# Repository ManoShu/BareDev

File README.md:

# BareDev - A small, yet resourceful keyboard

An open-source, QMK-compatible, ABNT2-based 70% keyboard, focusing in a smaller footprint while retaining all the functions found on a TKL (Del and arrow keys doubling as the navigational cluster)

---

Layout:

Links: [KLE](http://www.keyboard-layout-editor.com/#/gists/89e76130aa221e028ccd5b3f6dec0909), [JSON](https://gist.github.com/ManoShu/89e76130aa221e028ccd5b3f6dec0909), [QMK](https://github.com/qmk/qmk_firmware/tree/master/keyboards/handwired/baredev/rev1)

---

## PCB & Case

Note: this photo is of an early prototype of the case. The uploaded files has been updated to require less total area and WILL look slighty different than shown (the overall dimensions remain the same).

The case and gerber files are under `production`. The had been used and confirmed to work, however use them at your own risk.

## QMK

The rev1 has been integrated in the [main QMK repository](https://github.com/qmk/qmk_firmware/tree/master/keyboards/handwired/baredev/rev1), being able to use the [online configurator](https://config.qmk.fm/#/handwired/baredev/rev1/LAYOUT_abnt2) to generate the firmware while also having the files on the `qmk` directory here in case of you don't want to update your fork (HOWEVER the files have been confirmed working on QMK 0.2.2 [check yours with `qmk --version`], previous versions might not have support for some of the tags in the` info.json` file)

## VIA / VIAL

A `via` keymap is available allowing to use VIA to change keybindings without the need to setup QMK. 
It is not integrated with the official repository yet, but the .json file required to change bindings is available on the `via` directory.

A VIAL-compatible keymap is also available. It is on the official repository, but in case you don't want to update, just drop the keyboard folder to your `vial-qmk` directory and it should also work right off the bat.

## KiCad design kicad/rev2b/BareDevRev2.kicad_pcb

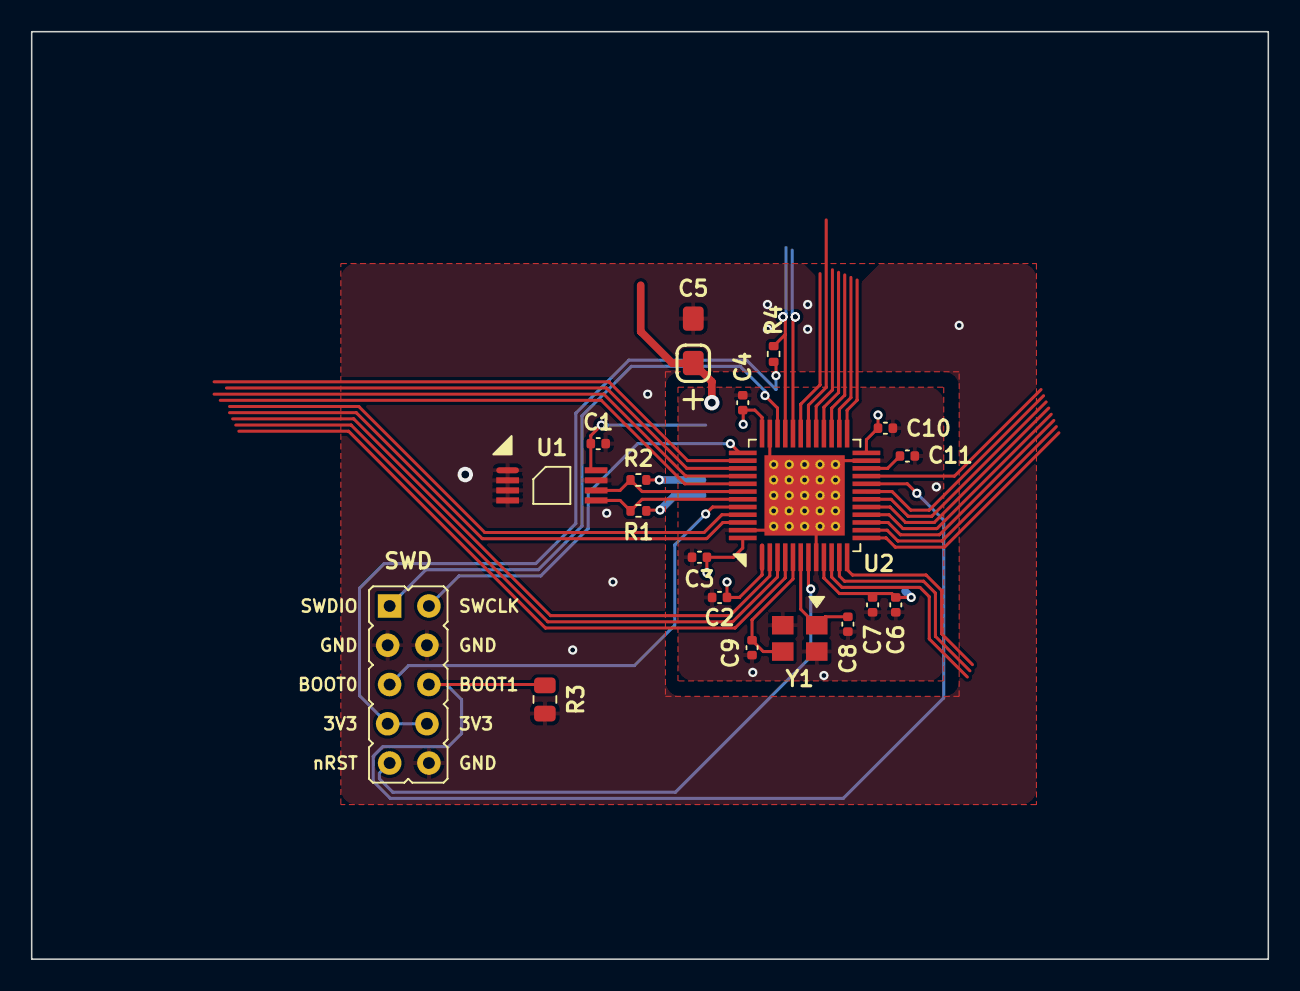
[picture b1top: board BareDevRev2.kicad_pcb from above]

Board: 2 copper layers, 80.0 x 60.0 mm, 19 parts (0 on the bottom side), 13 nets.

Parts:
C1, C2, C3, C4, C10: 100n; C_0402_1005Metric
C5: 10u; CP_EIA-3216-10_Kemet-I_Pad1.58x1.35mm_HandSolder
C6: 1u; C_0402_1005Metric
C7: 10n; C_0402_1005Metric
C8, C9: 16p; C_0402_1005Metric
C11: 4.7u; C_0402_1005Metric
R1, R2, R4: 1.5k; R_0402_1005Metric
R3: 10k; R_0805_2012Metric
U1: BL24C256A-SFRC; TSSOP-8_4.4x3mm_P0.65mm
U2: STM32F411CEU6; STM_UFQFPN-48_LQFP-48-1EP_7x7mm_P0.5mm_HandSoldering_Therma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
X1: ARM JTAG; PinHeader_2x5_P2.54mm_Vertical_Staggered
Y1: 7325-0800A2010-00; Crystal_SMD_3225-4Pin_3.2x2.5mm

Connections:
3V3: C1.2, C2.1, C3.1, C4.2, C5.1, C6.1, C7.1, C10.2, R1.1, R2.1, R4.1, U1.8 (VCC), U2.1 (VBAT), U2.9 (VDDA/VREF+), U2.24 (VDD), U2.36 (VDD), U2.48 (VDD), X1.7, X1.8
BOOT0: U2.44 (BOOT0), X1.5
D+: R4.2, U2.33 (PA12/USB_FS_DP)
GND: C1.1, C2.2, C3.2, C4.1, C5.2, C6.2, C7.2, C8.2, C9.2, C10.1, C11.1, R3.2, U1.1 (A0), U1.2 (A1), U1.3 (A2), U1.4 (GND), U1.7 (WP), U2.8 (VSSA), U2.23 (VSS), U2.35 (VSS), U2.47 (VSS), X1.3, X1.4, X1.10, Y1.2, Y1.4
NRST: U2.7 (NRST), X1.9
unnamed: C11.2, U2.22 (VCAP_1)
PB2/BOOT1: R3.1, U2.20 (PB2), X1.6
SCL: R2.2, U1.6 (SCL), U2.42 (PB6/I2C1_SCL)
SDA: R1.2, U1.5 (SDA), U2.43 (PB7/I2C1_SDA)
SWCLK: U2.37 (PA14/SWCLK), X1.2
SWDIO: U2.34 (PA12/SWDIO), X1.1
XTAL_IN: C9.1, U2.5 (PH0_OSCIN), Y1.3
XTAL_OUT: C8.1, U2.6 (PH1_OSCOUT), Y1.1

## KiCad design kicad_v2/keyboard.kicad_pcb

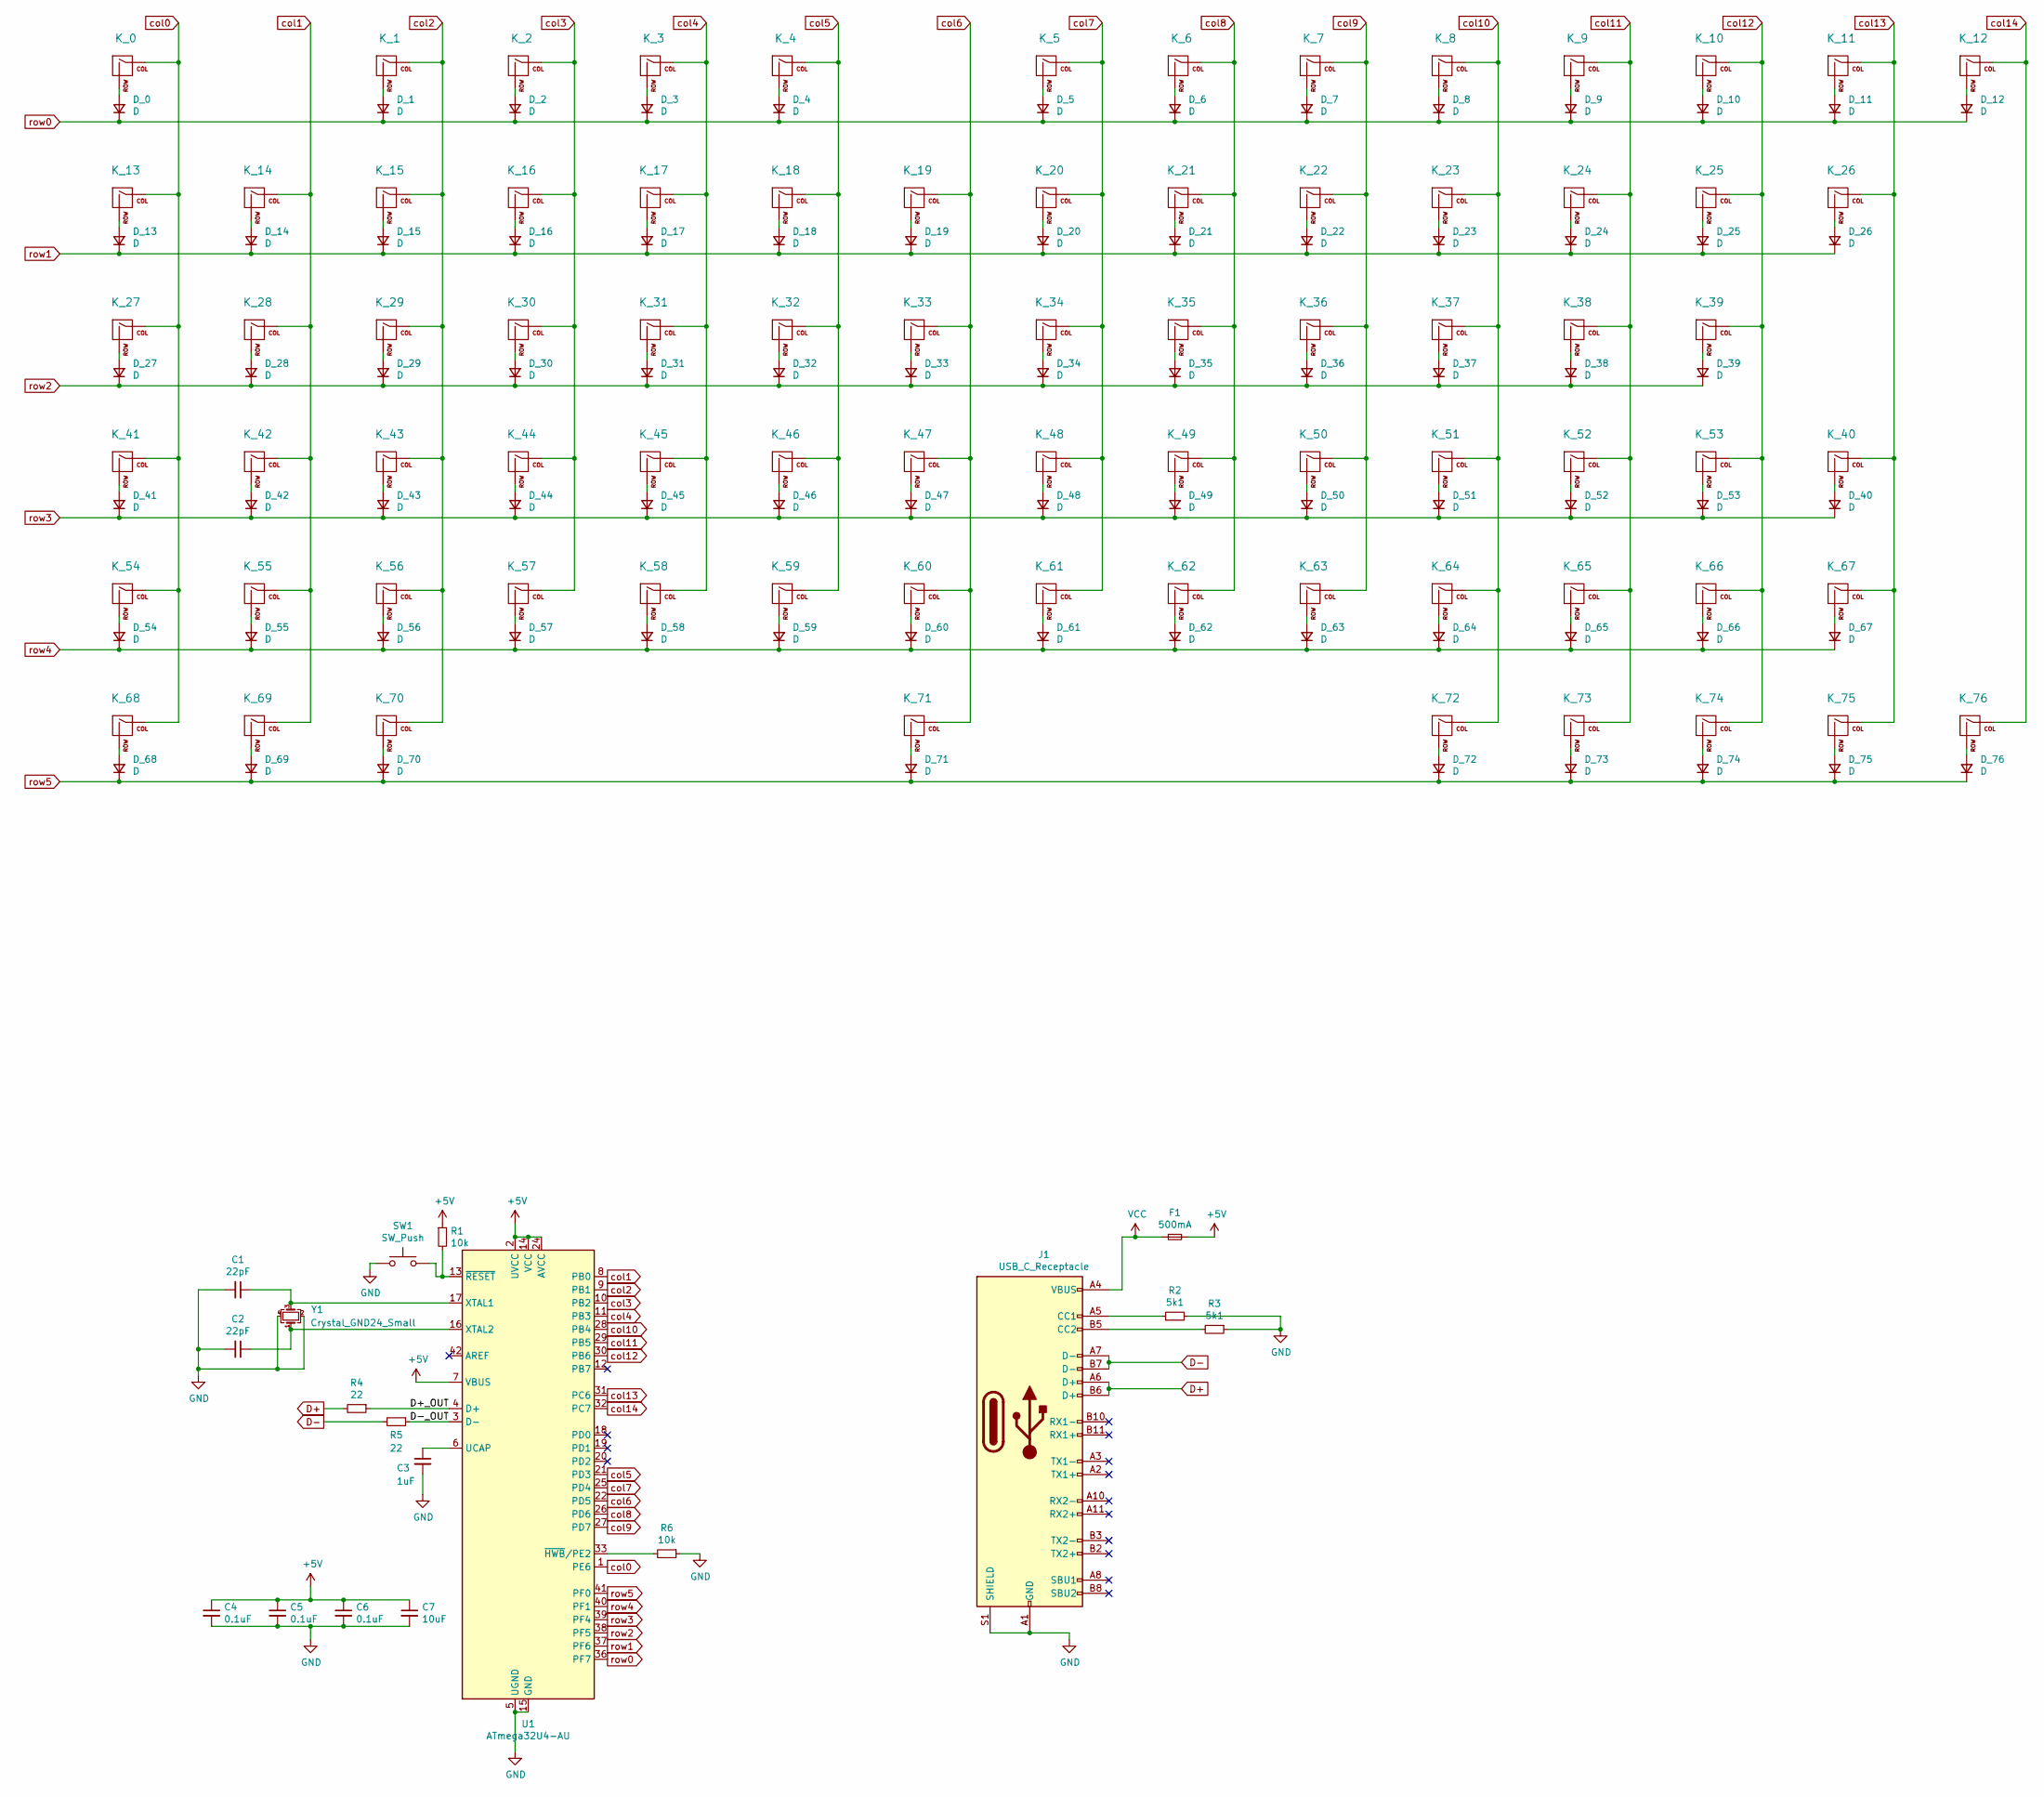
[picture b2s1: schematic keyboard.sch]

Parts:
C1, C2: 22pF; C_0805_2012Metric
C3: 1uF; C_0805_2012Metric
C4, C5, C6: 0.1uF; C_0805_2012Metric
C7: 10uF; C_0805_2012Metric
D_0, D_1, D_2, D_3, D_4, D_5, D_6, D_7, D_8, D_9, D_10, D_11, D_12, D_13, D_14, D_15, D_16, D_17, D_18, D_19, D_20, D_21, D_22, D_23, D_24, D_25, D_26, D_27, D_28, D_29, D_30, D_31, D_32, D_33, D_34, D_35, D_36, D_37, D_38, D_39, D_40, D_41, D_42, D_43, D_44, D_45, D_46, D_47, D_48, D_49, D_50, D_51, D_52, D_53, D_54, D_55, D_56, D_57, D_58, D_59, D_60, D_61, D_62, D_63, D_64, D_65, D_66, D_67, D_68, D_69, D_70, D_71, D_72, D_73, D_74, D_75, D_76: D; D_SOD-123
F1: 500mA; Fuse_1206_3216Metric
J1: USB_C_Receptacle; USB_C_Receptacle_HRO_TYPE-C-31-M-12; JLCPCB C167321
K_0, K_1, K_2, K_3, K_4, K_5, K_6, K_7, K_8, K_9, K_10, K_11, K_12, K_13, K_14, K_15, K_16, K_17, K_18, K_19, K_20, K_21, K_22, K_23, K_24, K_25, K_28, K_29, K_30, K_31, K_32, K_33, K_34, K_35, K_36, K_37, K_38, K_39, K_42, K_43, K_44, K_45, K_46, K_47, K_48, K_49, K_50, K_51, K_52, K_53, K_55, K_56, K_57, K_58, K_59, K_60, K_61, K_62, K_63, K_64, K_65, K_66, K_67, K_73, K_74, K_75, K_76: KEYSW; MXOnly-1U-Hotswap
K_26: KEYSW; MXOnly-2U-Hotswap
K_27: KEYSW; MXOnly-1.5U-Hotswap
K_40: KEYSW; MXOnly-ISO-NoLED-Hotswap
K_41: KEYSW; MXOnly-1.75U-Hotswap
K_54, K_68, K_69, K_70, K_72: KEYSW; MXOnly-1.25U-Hotswap
K_71: KEYSW; MXOnly-6.25U-Hotswap
R1, R6: 10k; R_0805_2012Metric
R2, R3: 5k1; R_0805_2012Metric
R4, R5: 22; R_0805_2012Metric
SW1: SW_Push; SKQG-1155865
U1: ATmega32U4-AU; TQFP-44_10x10mm_P0.8mm
Y1: Crystal_GND24_Small; Crystal_SMD_3225-4Pin_3.2x2.5mm

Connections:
+5V: C4.1, C5.1, C6.1, C7.1, F1.2, R1.1, U1.2 (UVCC), U1.7 (VBUS), U1.14 (VCC), U1.24 (AVCC), U1.34 (VCC), U1.44 (AVCC)
/D+_OUT: R4.1, U1.4 (D+)
/D-_OUT: R5.1, U1.3 (D-)
D+: J1.A6 (D+), J1.B6 (D+), R4.2
D-: J1.A7 (D-), J1.B7 (D-), R5.2
GND: C1.2, C2.2, C3.2, C4.2, C5.2, C6.2, C7.2, J1.A1 (GND), J1.A12 (GND), J1.B1 (GND), J1.B12 (GND), J1.S1 (SHIELD), R2.2, R3.1, R6.1, SW1.1, U1.5 (UGND), U1.15 (GND), U1.23 (GND), U1.35 (GND), U1.43 (GND), Y1.2, Y1.4
unnamed: C1.1, U1.17 (XTAL1), Y1.3
unnamed: C2.1, U1.16 (XTAL2), Y1.1
unnamed: C3.1, U1.6 (UCAP)
unnamed: D_0.2 (A), K_0.2 (ROW)
unnamed: D_1.2 (A), K_1.2 (ROW)
unnamed: D_2.2 (A), K_2.2 (ROW)
unnamed: D_3.2 (A), K_3.2 (ROW)
unnamed: D_4.2 (A), K_4.2 (ROW)
unnamed: D_5.2 (A), K_5.2 (ROW)
unnamed: D_6.2 (A), K_6.2 (ROW)
unnamed: D_7.2 (A), K_7.2 (ROW)
unnamed: D_8.2 (A), K_8.2 (ROW)
unnamed: D_9.2 (A), K_9.2 (ROW)
unnamed: D_10.2 (A), K_10.2 (ROW)
unnamed: D_11.2 (A), K_11.2 (ROW)
unnamed: D_12.2 (A), K_12.2 (ROW)
unnamed: D_13.2 (A), K_13.2 (ROW)
unnamed: D_14.2 (A), K_14.2 (ROW)
unnamed: D_15.2 (A), K_15.2 (ROW)
unnamed: D_16.2 (A), K_16.2 (ROW)
unnamed: D_17.2 (A), K_17.2 (ROW)
unnamed: D_18.2 (A), K_18.2 (ROW)
unnamed: D_19.2 (A), K_19.2 (ROW)
unnamed: D_20.2 (A), K_20.2 (ROW)
unnamed: D_21.2 (A), K_21.2 (ROW)
unnamed: D_22.2 (A), K_22.2 (ROW)
unnamed: D_23.2 (A), K_23.2 (ROW)
unnamed: D_24.2 (A), K_24.2 (ROW)
unnamed: D_25.2 (A), K_25.2 (ROW)
unnamed: D_26.2 (A), K_26.2 (ROW)
unnamed: D_27.2 (A), K_27.2 (ROW)
unnamed: D_28.2 (A), K_28.2 (ROW)
unnamed: D_29.2 (A), K_29.2 (ROW)
unnamed: D_30.2 (A), K_30.2 (ROW)
unnamed: D_31.2 (A), K_31.2 (ROW)
unnamed: D_32.2 (A), K_32.2 (ROW)
unnamed: D_33.2 (A), K_33.2 (ROW)
unnamed: D_34.2 (A), K_34.2 (ROW)
unnamed: D_35.2 (A), K_35.2 (ROW)
unnamed: D_36.2 (A), K_36.2 (ROW)
unnamed: D_37.2 (A), K_37.2 (ROW)
unnamed: D_38.2 (A), K_38.2 (ROW)
unnamed: D_39.2 (A), K_39.2 (ROW)
unnamed: D_40.2 (A), K_40.2 (ROW)
unnamed: D_41.2 (A), K_41.2 (ROW)
unnamed: D_42.2 (A), K_42.2 (ROW)
unnamed: D_43.2 (A), K_43.2 (ROW)
unnamed: D_44.2 (A), K_44.2 (ROW)
unnamed: D_45.2 (A), K_45.2 (ROW)
unnamed: D_46.2 (A), K_46.2 (ROW)
unnamed: D_47.2 (A), K_47.2 (ROW)
unnamed: D_48.2 (A), K_48.2 (ROW)
unnamed: D_49.2 (A), K_49.2 (ROW)
unnamed: D_50.2 (A), K_50.2 (ROW)
unnamed: D_51.2 (A), K_51.2 (ROW)
unnamed: D_52.2 (A), K_52.2 (ROW)
unnamed: D_53.2 (A), K_53.2 (ROW)
unnamed: D_54.2 (A), K_54.2 (ROW)
unnamed: D_55.2 (A), K_55.2 (ROW)
unnamed: D_56.2 (A), K_56.2 (ROW)
unnamed: D_57.2 (A), K_57.2 (ROW)
unnamed: D_58.2 (A), K_58.2 (ROW)
unnamed: D_59.2 (A), K_59.2 (ROW)
unnamed: D_60.2 (A), K_60.2 (ROW)
unnamed: D_61.2 (A), K_61.2 (ROW)
unnamed: D_62.2 (A), K_62.2 (ROW)
unnamed: D_63.2 (A), K_63.2 (ROW)
unnamed: D_64.2 (A), K_64.2 (ROW)
unnamed: D_65.2 (A), K_65.2 (ROW)
unnamed: D_66.2 (A), K_66.2 (ROW)
unnamed: D_67.2 (A), K_67.2 (ROW)
unnamed: D_68.2 (A), K_68.2 (ROW)
unnamed: D_69.2 (A), K_69.2 (ROW)
unnamed: D_70.2 (A), K_70.2 (ROW)
unnamed: D_71.2 (A), K_71.2 (ROW)
unnamed: D_72.2 (A), K_72.2 (ROW)
unnamed: D_73.2 (A), K_73.2 (ROW)
unnamed: D_74.2 (A), K_74.2 (ROW)
unnamed: D_75.2 (A), K_75.2 (ROW)
unnamed: D_76.2 (A), K_76.2 (ROW)
unnamed: J1.A5 (CC1), R2.1
unnamed: J1.B5 (CC2), R3.2
unnamed: R1.2, SW1.2, U1.13 (~RESET)
unnamed: R6.2, U1.33 (~HWB~/PE2)
VCC: F1.1, J1.A4 (VBUS), J1.A9 (VBUS), J1.B4 (VBUS), J1.B9 (VBUS)
col0: K_0.1 (COL), K_13.1 (COL), K_27.1 (COL), K_41.1 (COL), K_54.1 (COL), K_68.1 (COL), U1.1 (PE6)
col1: K_14.1 (COL), K_28.1 (COL), K_42.1 (COL), K_55.1 (COL), K_69.1 (COL), U1.8 (PB0)
col2: K_1.1 (COL), K_15.1 (COL), K_29.1 (COL), K_43.1 (COL), K_56.1 (COL), K_70.1 (COL), U1.9 (PB1)
col3: K_2.1 (COL), K_16.1 (COL), K_30.1 (COL), K_44.1 (COL), K_57.1 (COL), U1.10 (PB2)
col4: K_3.1 (COL), K_17.1 (COL), K_31.1 (COL), K_45.1 (COL), K_58.1 (COL), U1.11 (PB3)
col5: K_4.1 (COL), K_18.1 (COL), K_32.1 (COL), K_46.1 (COL), K_59.1 (COL), U1.21 (PD3)
col6: K_19.1 (COL), K_33.1 (COL), K_47.1 (COL), K_60.1 (COL), K_71.1 (COL), U1.22 (PD5)
col7: K_5.1 (COL), K_20.1 (COL), K_34.1 (COL), K_48.1 (COL), K_61.1 (COL), U1.25 (PD4)
col8: K_6.1 (COL), K_21.1 (COL), K_35.1 (COL), K_49.1 (COL), K_62.1 (COL), U1.26 (PD6)
col9: K_7.1 (COL), K_22.1 (COL), K_36.1 (COL), K_50.1 (COL), K_63.1 (COL), U1.27 (PD7)
col10: K_8.1 (COL), K_23.1 (COL), K_37.1 (COL), K_51.1 (COL), K_64.1 (COL), K_72.1 (COL), U1.28 (PB4)
col11: K_9.1 (COL), K_24.1 (COL), K_38.1 (COL), K_52.1 (COL), K_65.1 (COL), K_73.1 (COL), U1.29 (PB5)
col12: K_10.1 (COL), K_25.1 (COL), K_39.1 (COL), K_53.1 (COL), K_66.1 (COL), K_74.1 (COL), U1.30 (PB6)
col13: K_11.1 (COL), K_26.1 (COL), K_40.1 (COL), K_67.1 (COL), K_75.1 (COL), U1.31 (PC6)
col14: K_12.1 (COL), K_76.1 (COL), U1.32 (PC7)
row0: D_0.1 (K), D_1.1 (K), D_2.1 (K), D_3.1 (K), D_4.1 (K), D_5.1 (K), D_6.1 (K), D_7.1 (K), D_8.1 (K), D_9.1 (K), D_10.1 (K), D_11.1 (K), D_12.1 (K), U1.36 (PF7)
row1: D_13.1 (K), D_14.1 (K), D_15.1 (K), D_16.1 (K), D_17.1 (K), D_18.1 (K), D_19.1 (K), D_20.1 (K), D_21.1 (K), D_22.1 (K), D_23.1 (K), D_24.1 (K), D_25.1 (K), D_26.1 (K), U1.37 (PF6)
row2: D_27.1 (K), D_28.1 (K), D_29.1 (K), D_30.1 (K), D_31.1 (K), D_32.1 (K), D_33.1 (K), D_34.1 (K), D_35.1 (K), D_36.1 (K), D_37.1 (K), D_38.1 (K), D_39.1 (K), U1.38 (PF5)
row3: D_40.1 (K), D_41.1 (K), D_42.1 (K), D_43.1 (K), D_44.1 (K), D_45.1 (K), D_46.1 (K), D_47.1 (K), D_48.1 (K), D_49.1 (K), D_50.1 (K), D_51.1 (K), D_52.1 (K), D_53.1 (K), U1.39 (PF4)
row4: D_54.1 (K), D_55.1 (K), D_56.1 (K), D_57.1 (K), D_58.1 (K), D_59.1 (K), D_60.1 (K), D_61.1 (K), D_62.1 (K), D_63.1 (K), D_64.1 (K), D_65.1 (K), D_66.1 (K), D_67.1 (K), U1.40 (PF1)
row5: D_68.1 (K), D_69.1 (K), D_70.1 (K), D_71.1 (K), D_72.1 (K), D_73.1 (K), D_74.1 (K), D_75.1 (K), D_76.1 (K), U1.41 (PF0)

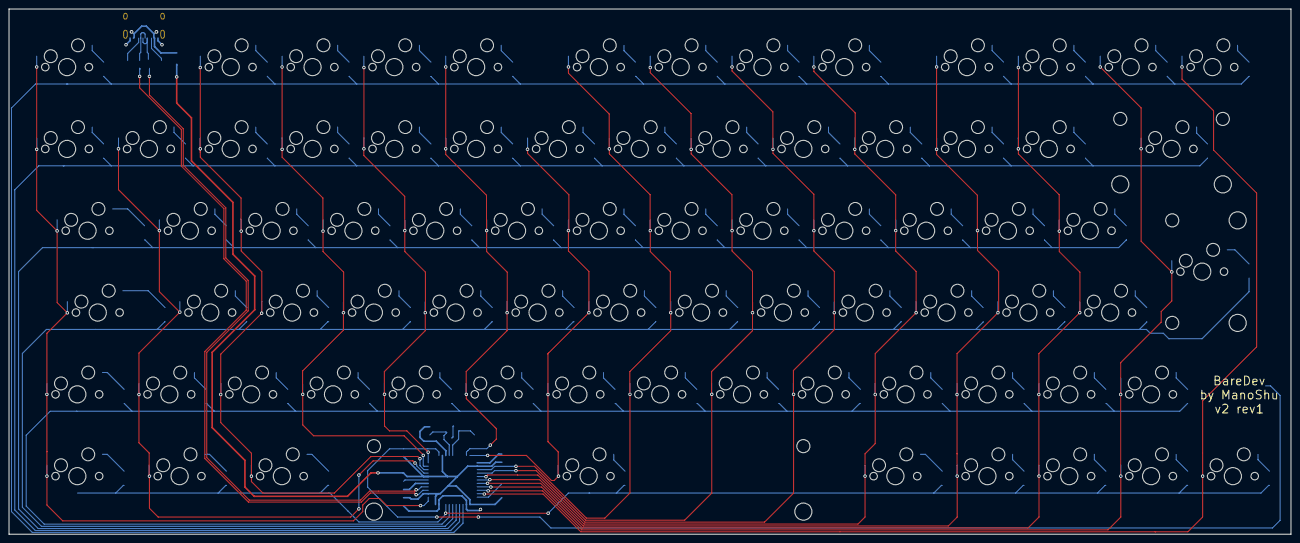
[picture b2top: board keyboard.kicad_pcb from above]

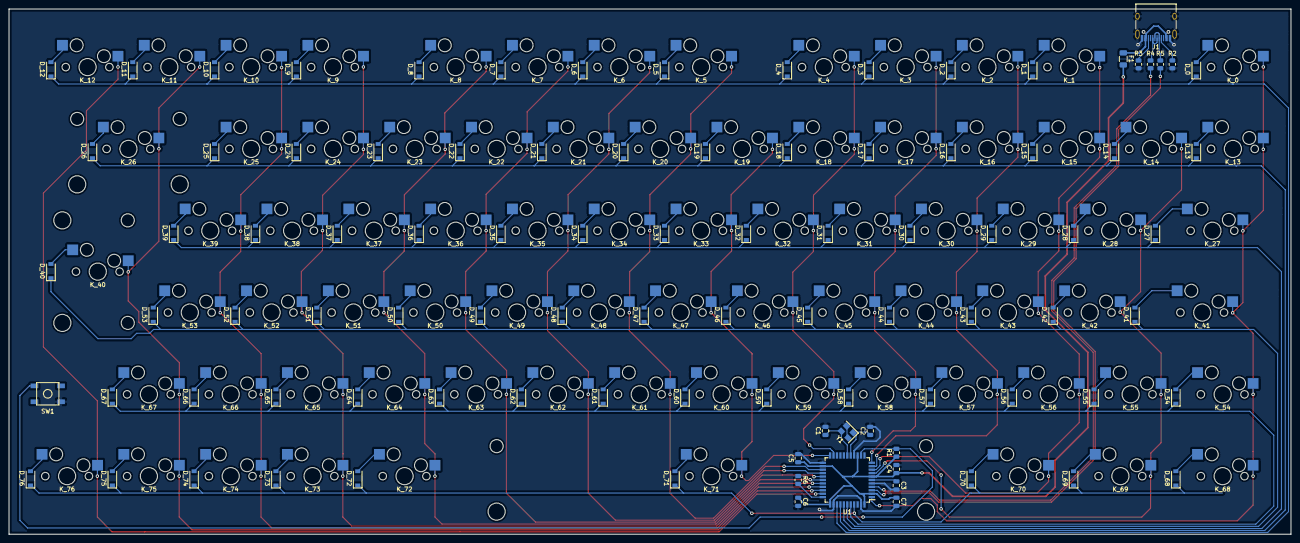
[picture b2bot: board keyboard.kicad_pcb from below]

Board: 2 copper layers, 298.5 x 122.3 mm, 172 parts (95 on the bottom side), 112 nets.

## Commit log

2021-07-15 Adding base kicad files (not working yet)
2021-07-22 Updated project
2021-07-22 Schematic complete
2021-07-23 1st version of PCB complete
2021-07-23 Revised traces
2021-07-23 Added production files and added text to PCB
2021-07-23 Added position file
2021-07-24 Fixed BOM to use reference the correct connector
2021-07-24 Updated part name for USB connector
2021-07-24 Added v2 directory
2021-07-26 v2 board DRC cleared
2021-07-26 Added text
2021-12-17 Saving
    Former-commit-id: 2b9b2436ad6caaab3dc3530084eb5f21174a8620
2021-12-17 Directory tree rework to start rev2 development
    Former-commit-id: 18c596bd722c1b8838767bc8a1715bf582b47f4a
2022-01-14 Uploaded QMK and case files; README update
    Former-commit-id: 6f7f39cc7777f5bec9c2551d6fcce16e323bc2d0
2022-01-14 Added VIA json file
    Former-commit-id: bcb08c1814aef6ef72b645727e384d02b57af465
2022-01-14 Moved README.md images to local source
    Former-commit-id: 82f2e3490f3ea9fc848d3c832f99d755f3c45b5b
2022-02-15 Updated vendor ID
    Former-commit-id: 013484da228be1b504a01d369143fb686b07949f
2022-02-15 Adding vial keymap
    Former-commit-id: 7e5843d0aa6f24730d5e9a054747b0a081d2e4ab
2022-02-15 Updated README with via/vial information
    Former-commit-id: 482b3c5e7cfa93c5fc339b5631f88273785b3341
2022-02-18 Fixed missing 'Don't connect's in schematic
2022-02-18 Initial rev2 development
2022-02-21 rev2 base PCB done
2022-02-21 base rev2 PCB done
2022-02-22 rev2 PCB finished
2022-02-22 Applied major silk screen drawings
2022-03-02 Updated PCB file
2022-03-02 Renaming rev2 folder to work on a STM version
2022-03-02 Adding rev2b base files
2022-03-02 Updated .gitmodules (???)
2022-03-02 Added MX_Alps_Hybrid submodule
2022-03-02 initial rev2b schematic
2022-03-03 Refactored matrix and LED grids
2022-03-04 (WIP) rev2b work
2022-03-04 rev2b routing done (production files not working with JLCPCB
2022-03-04 Removing unreliable production files
2022-03-05 Added production files (not yet confirmed working)
2022-03-05 Adding assembly files (not yet tested)
2022-03-06 Art vector inserted (sadly overlapping)
2022-03-07 Updated production files
